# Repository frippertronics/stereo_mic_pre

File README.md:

This repository contains KiCAD design files for a stereo microphone pre-amplifier targeting the Church Audio CA-11. 

The pre-amp delivers a 5V bias voltage to the microphone, and features padding and a fixed gain.

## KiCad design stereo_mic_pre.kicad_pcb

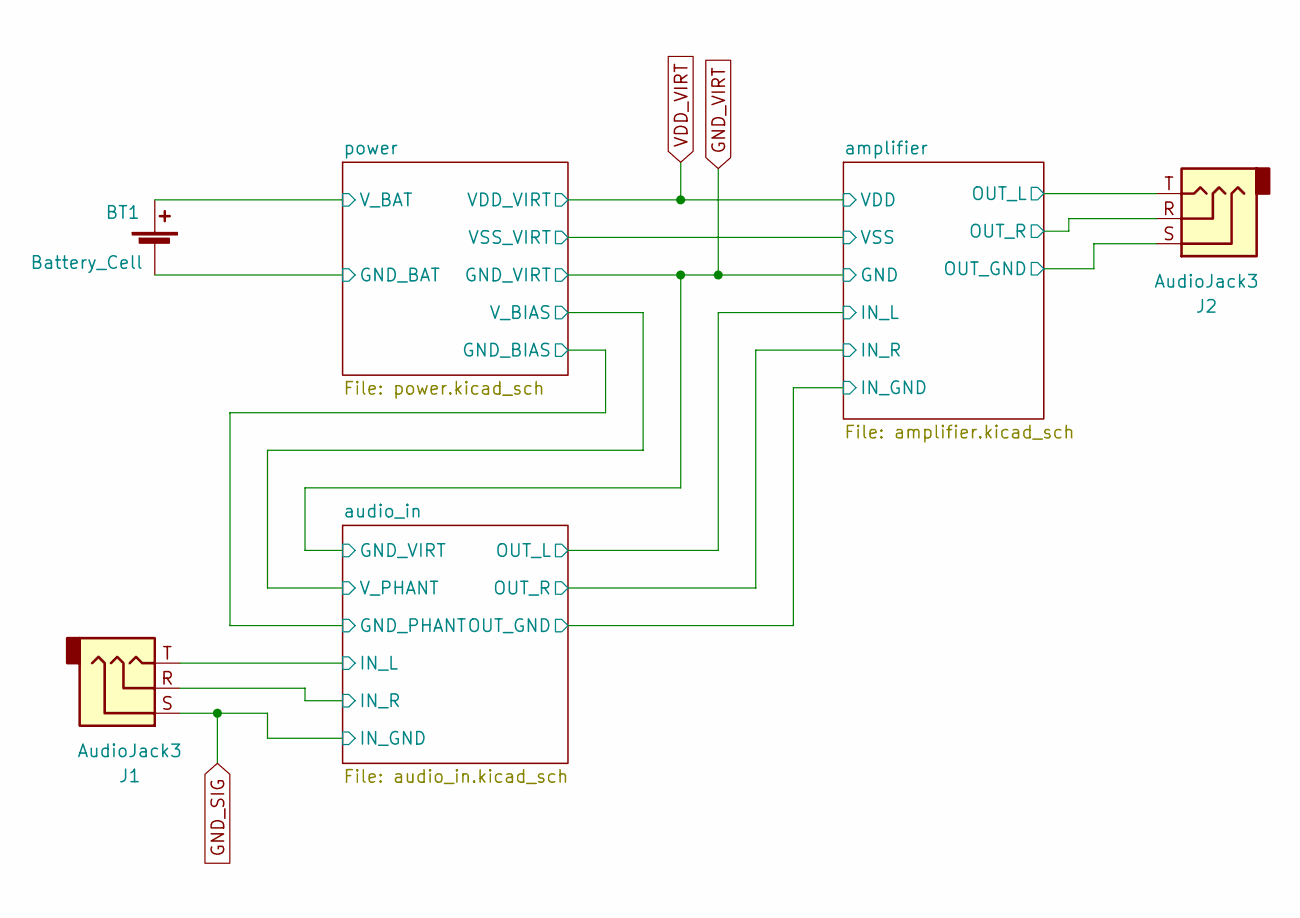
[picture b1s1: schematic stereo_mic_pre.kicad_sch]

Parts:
BT1: Battery_Cell; BatteryHolder_Eagle_12BH611-GR
J1, J2: AudioJack3; Jack_3.5mm_CUI_SJ1-3533NG_Horizontal

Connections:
-4V5: J1.S, J2.S; also elsewhere on the board
/amplifier/OUT_L: J2.T; also elsewhere on the board
/amplifier/OUT_R: J2.R; also elsewhere on the board
/audio_in/IN_L: J1.T; also elsewhere on the board
/audio_in/IN_R: J1.R; also elsewhere on the board
/power/GND_BAT: BT1.2 (-); also elsewhere on the board
/power/V_BAT: BT1.1 (+); also elsewhere on the board

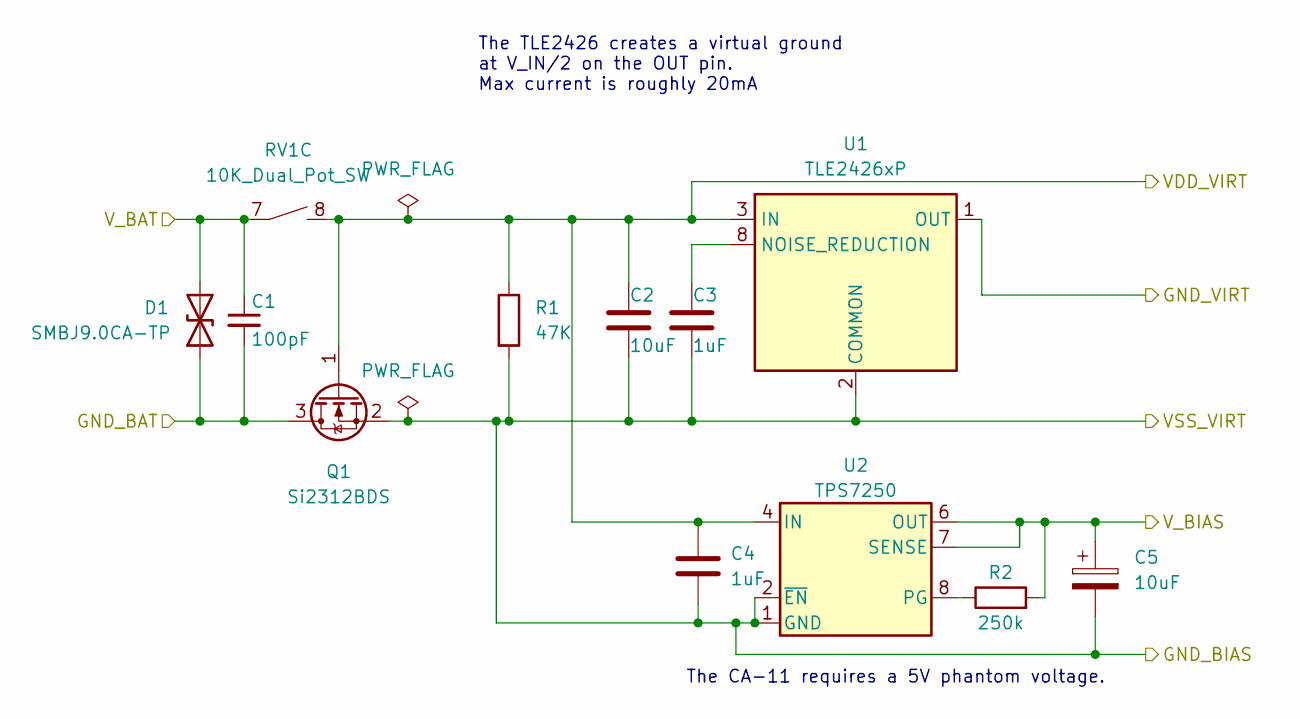
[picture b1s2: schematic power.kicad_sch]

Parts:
C1: 100pF; C_0603_1608Metric
C2, C5: 10uF; C_1206_3216Metric
C3, C4: 1uF; C_1206_3216Metric
D1: SMBJ9.0CA-TP; D_SMB_Handsoldering
Q1: Si2312BDS; SOT-23_Handsoldering
R1: 47K; C_0603_1608Metric
R2: 250k; C_0603_1608Metric
RV1: 10K_Dual_Pot_SW; Potentiometer_Bourns_PTR902_Double_Horizontal_Switch
U1: TLE2426xP; DIP-8_W7.62mm
U2: TPS7250; SMDIP-8_W9.53mm

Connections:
-4V5: C2.2, C3.2, C4.2, C5.2, Q1.2 (S), R1.2, U1.2 (COMMON), U2.1 (GND), U2.2 (~EN); also elsewhere on the board
/audio_in/V_PHANT: C5.1, R2.2, U2.5 (OUT), U2.6 (OUT), U2.7 (SENSE); also elsewhere on the board
/power/GND_BAT: C1.2, D1.1 (A1), Q1.3 (D); also elsewhere on the board
/power/V_BAT: C1.1, D1.2 (A2), RV1.7; also elsewhere on the board
GND_VIRT: U1.1 (OUT); also elsewhere on the board
unnamed: C3.1, U1.8 (NOISE_REDUCTION)
unnamed: R2.1, U2.8 (PG)
VDD_VIRT: C2.1, C4.1, Q1.1 (G), R1.1, RV1.8, U1.3 (IN), U2.3 (IN), U2.4 (IN); also elsewhere on the board

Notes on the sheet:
The CA-11 requires a 5V phantom voltage.
The TLE2426 creates a virtual ground at V_IN/2 on the OUT pin. Max current is roughly 20mA

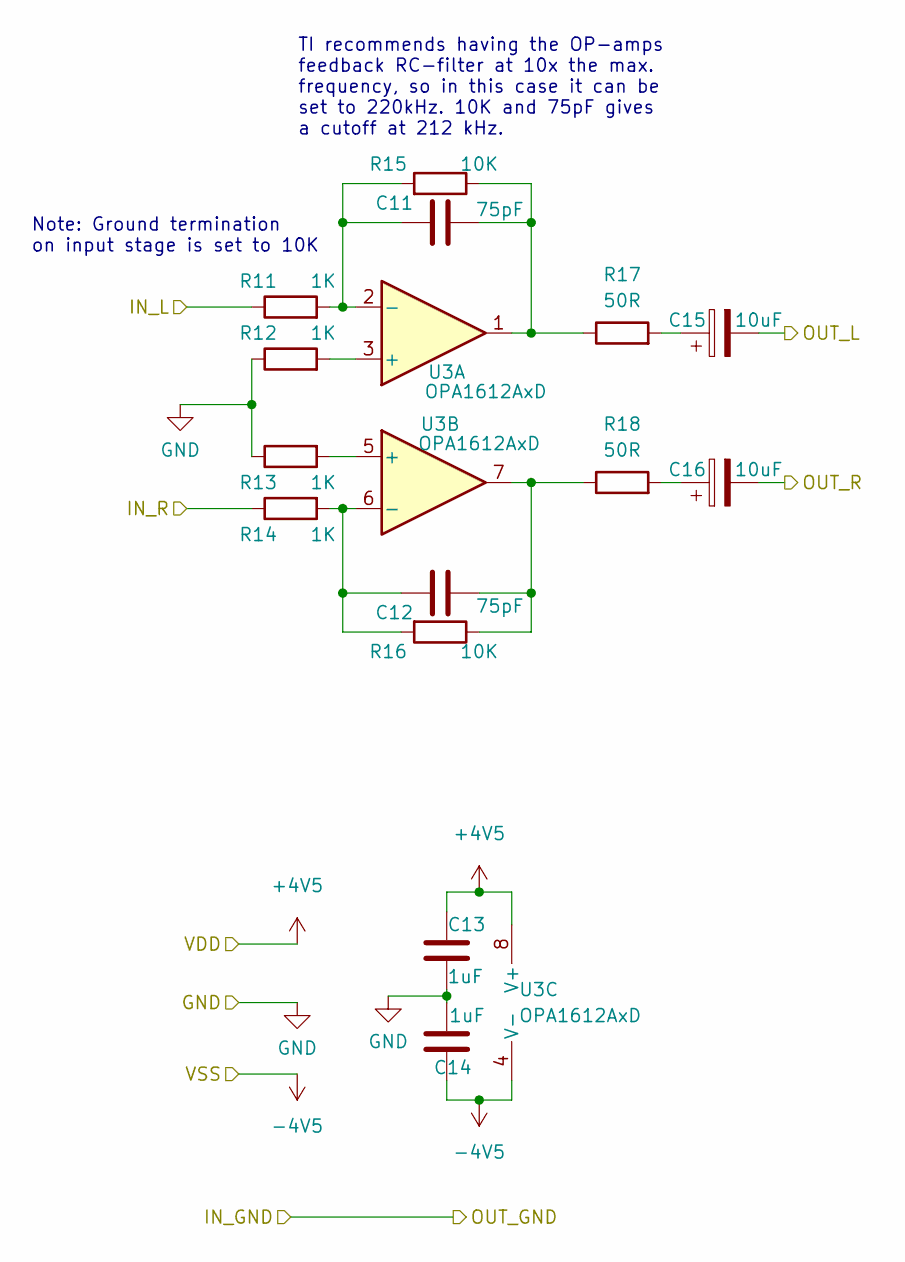
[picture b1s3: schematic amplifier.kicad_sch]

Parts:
C11, C12: 75pF; C_0603_1608Metric
C13, C14: 1uF; C_1206_3216Metric
C15, C16: 10uF; CP_Radial_D8.0mm_P3.50mm
R11, R12, R13, R14: 1K; C_0603_1608Metric
R15, R16: 10K; C_0603_1608Metric
R17, R18: 50R; C_0603_1608Metric
U3: OPA1612AxD; SOIC-8-1EP_3.9x4.9mm_P1.27mm_EP2.29x3mm_Wide

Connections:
-4V5: C14.1, U3.4 (V-); also elsewhere on the board
/amplifier/IN_L: R11.1; also elsewhere on the board
/amplifier/IN_R: R14.1; also elsewhere on the board
/amplifier/OUT_L: C15.2; also elsewhere on the board
/amplifier/OUT_R: C16.2; also elsewhere on the board
GND_VIRT: C13.2, C14.2, R12.1, R13.1; also elsewhere on the board
unnamed: C11.2, R15.1, R17.1, U3.1
unnamed: C12.2, R16.1, R18.1, U3.7
unnamed: C15.1, R17.2
unnamed: C16.1, R18.2
unnamed: R12.2, U3.3 (+)
unnamed: C11.1, R11.2, R15.2, U3.2 (-)
unnamed: R13.2, U3.5 (+)
unnamed: C12.1, R14.2, R16.2, U3.6 (-)
VDD_VIRT: C13.1, U3.8 (V+); also elsewhere on the board

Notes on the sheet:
TI recommends having the OP-amps feedback RC-filter at 10x the max. frequency, so in this case it can be set to 220kHz. 10K and 75pF gives a cutoff at 212 kHz.
Note: Ground termination on input stage is set to 10K

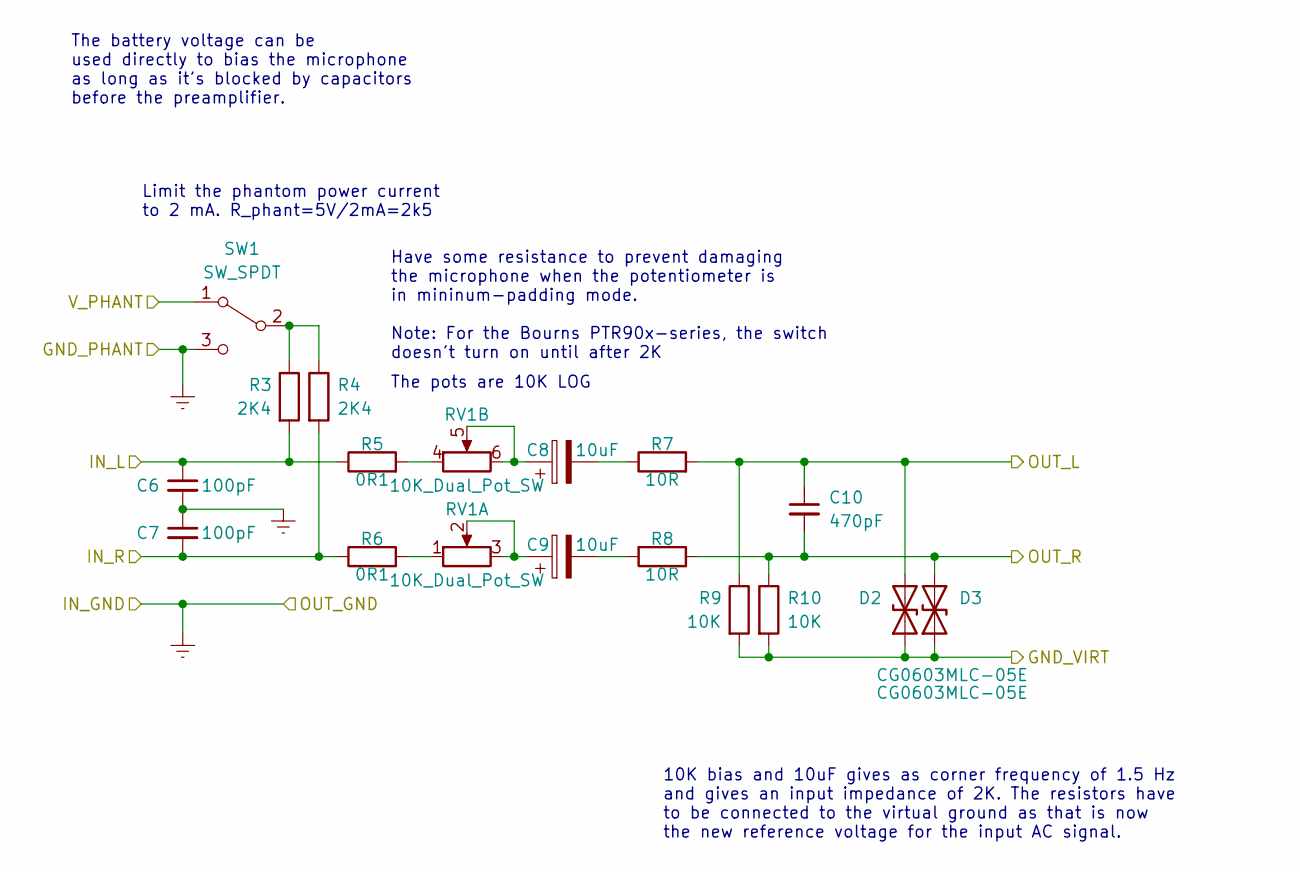
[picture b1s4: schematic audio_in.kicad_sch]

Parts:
C6, C7: 100pF; C_0603_1608Metric
C8, C9: 10uF; CP_Radial_D8.0mm_P3.50mm
C10: 470pF; C_0603_1608Metric
D2, D3: CG0603MLC-05E; D_0603_1608Metric_Pad1.05x0.95mm_HandSolder
R3, R4: 2K4; C_0603_1608Metric
R5, R6: 0R1; C_0603_1608Metric
R7, R8: 10R; C_0603_1608Metric
R9, R10: 10K; C_0603_1608Metric
RV1: 10K_Dual_Pot_SW; Potentiometer_Bourns_PTR902_Double_Horizontal_Switch
SW1: SW_SPDT; SW_CuK_OS102011MS2QN1_SPDT_Straight

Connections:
-4V5: C6.2, C7.1, SW1.3 (C); also elsewhere on the board
/amplifier/IN_L: C10.1, D2.2 (A2), R7.2, R9.1; also elsewhere on the board
/amplifier/IN_R: C10.2, D3.2 (A2), R8.2, R10.1; also elsewhere on the board
/audio_in/IN_L: C6.1, R3.2, R5.1; also elsewhere on the board
/audio_in/IN_R: C7.2, R4.2, R6.1; also elsewhere on the board
/audio_in/V_PHANT: SW1.1 (A); also elsewhere on the board
GND_VIRT: D2.1 (A1), D3.1 (A1), R9.2, R10.2; also elsewhere on the board
unnamed: C8.1, RV1.5, RV1.6
unnamed: C8.2, R7.1
unnamed: C9.2, R8.1
unnamed: R5.2, RV1.4
unnamed: C9.1, RV1.2, RV1.3 (7)
unnamed: R6.2, RV1.1 (8)
unnamed: R3.1, R4.1, SW1.2 (B)

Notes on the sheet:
The battery voltage can be used directly to bias the microphone as long as it's blocked by capacitors before the preamplifier.
10K bias and 10uF gives as corner frequency of 1.5 Hz and gives an input impedance of 2K. The resistors have to be connected to the virtual ground as that is now the new reference voltage for the input AC signal.
Limit the phantom power current to 2 mA. R_phant=5V/2mA=2k5
The pots are 10K LOG
Have some resistance to prevent damaging the microphone when the potentiometer is in mininum-padding mode. Note: For the Bourns PTR90x-series, the switch doesn't turn on until after 2K

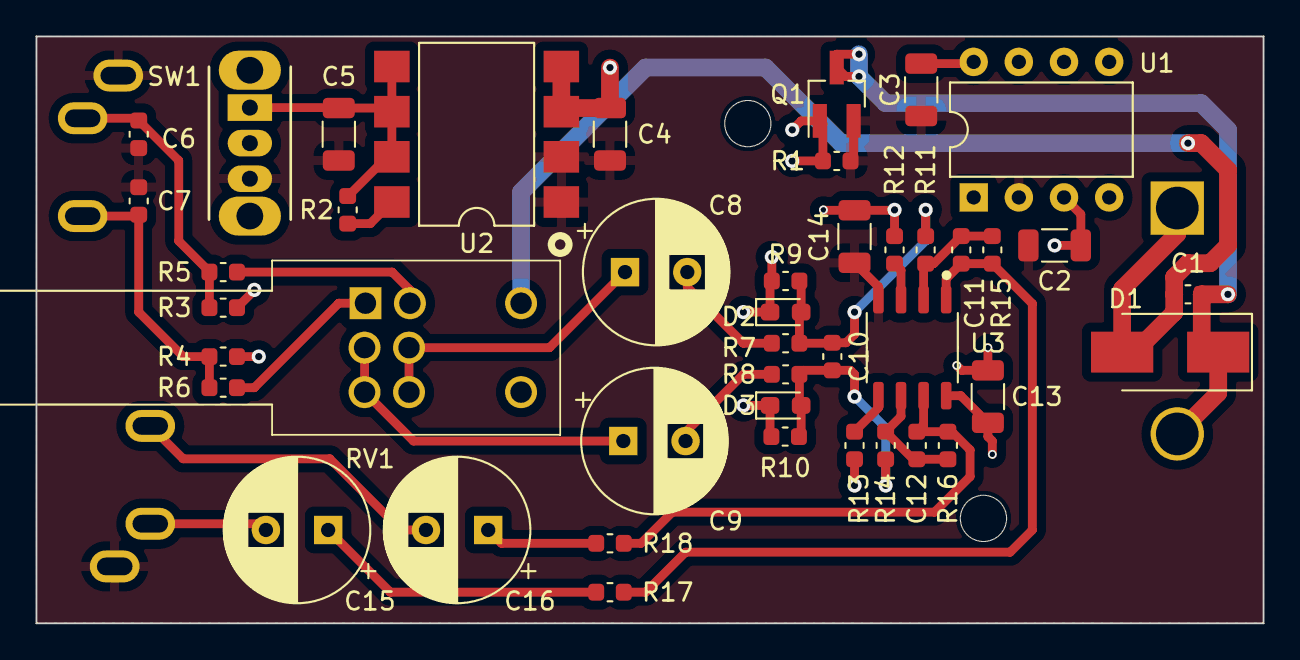
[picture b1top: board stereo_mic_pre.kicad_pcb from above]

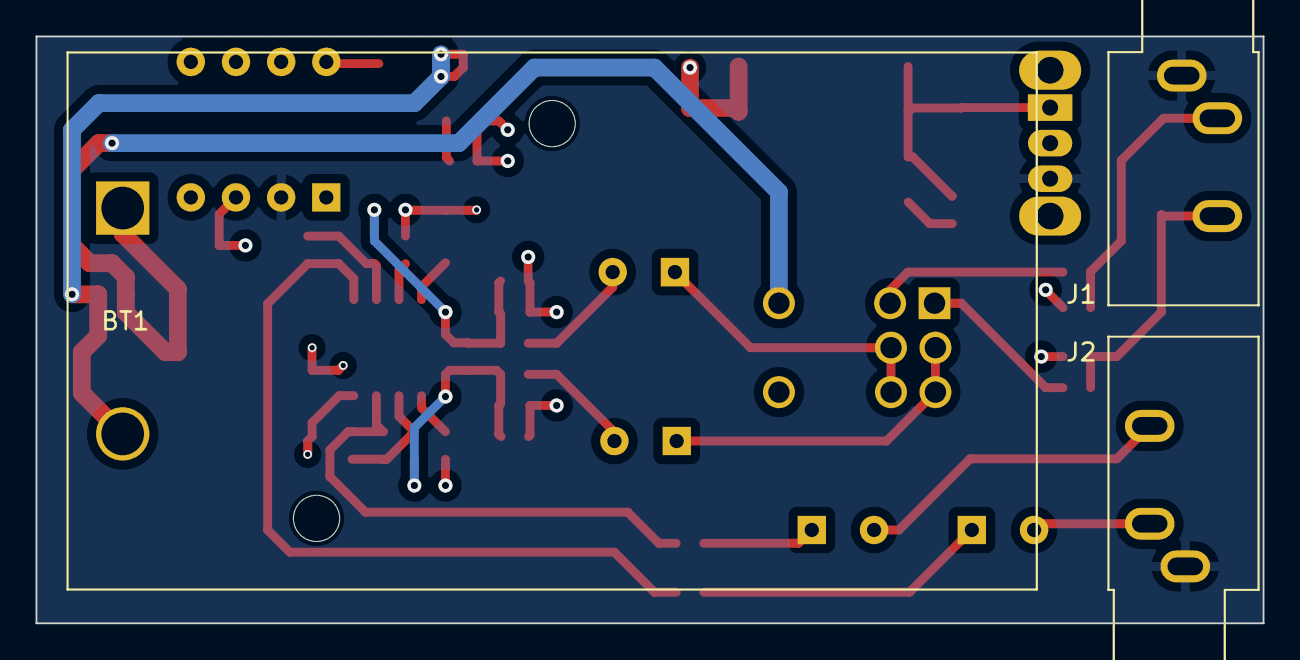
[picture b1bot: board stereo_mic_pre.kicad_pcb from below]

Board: 4 copper layers, 69.0 x 33.0 mm, 46 parts (3 on the bottom side), 29 nets.

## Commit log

2022-12-05 Initial commit with first schematic draft w/footprints
2023-01-31 Almost finished 2-layer routing, not sure about power/ground layers though
2023-03-06 Updated project to KiCAD 7.0
2023-03-06 Changed D2 and D3 to smaller 0603 diode, changed and rerouted for 4 layers
2023-03-07 Finished placing refdes, fix DRC errors
